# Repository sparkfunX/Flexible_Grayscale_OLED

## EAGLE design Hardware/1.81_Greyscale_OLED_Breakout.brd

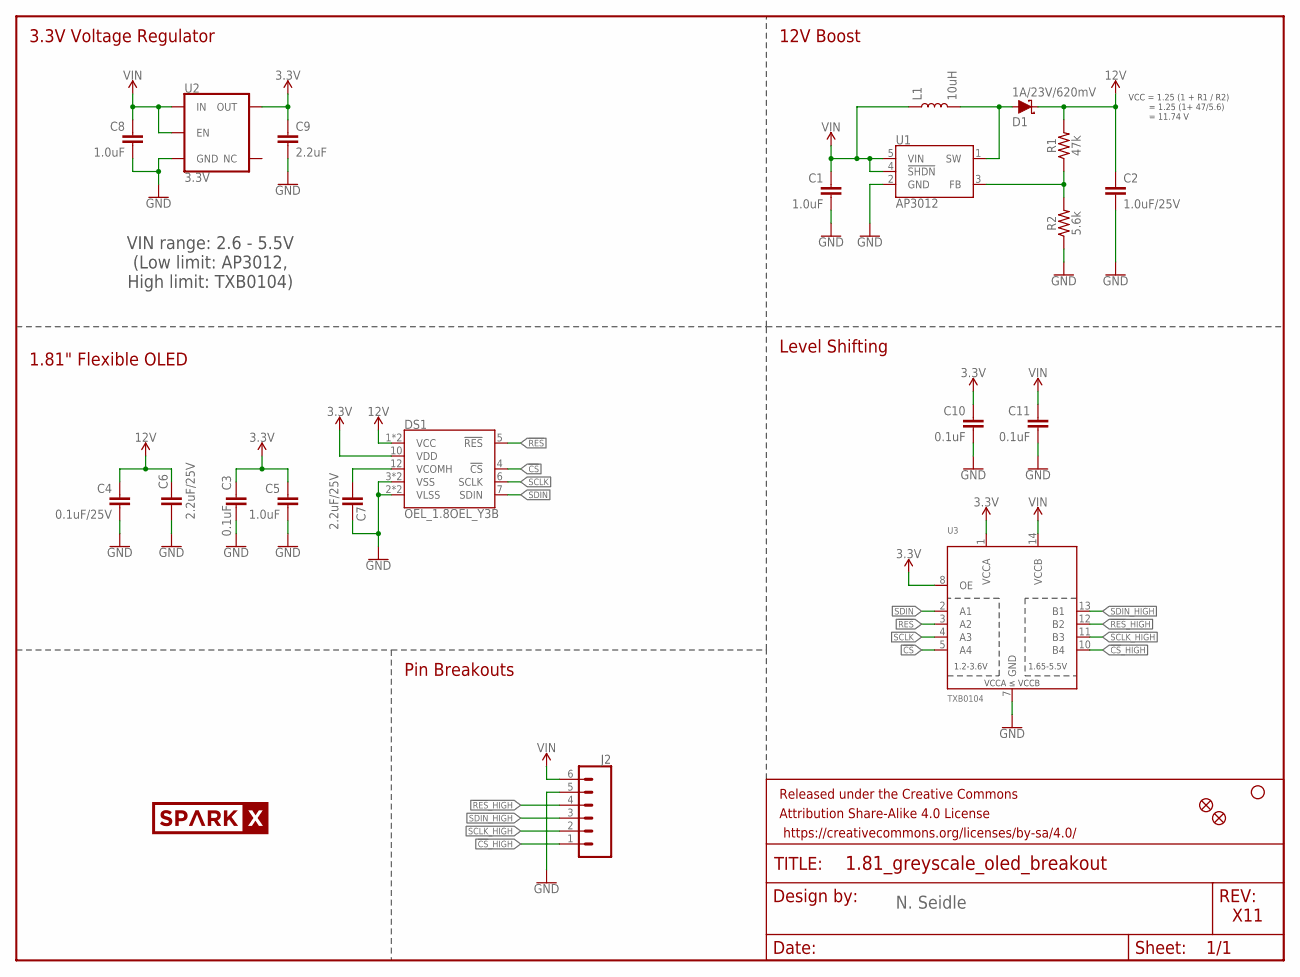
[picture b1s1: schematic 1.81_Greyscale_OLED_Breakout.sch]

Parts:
C1, C5, C8: 1.0uF; 0603
C2: 1.0uF/25V; 0805
C3, C10, C11: 0.1uF; 0603
C4: 0.1uF/25V; 0603
C6, C7: 2.2uF/25V; 0805
C9: 2.2uF; 0603
D1: 1A/23V/620mV; SOD-323
DS1: OEL_1.8OEL_Y3B; OEL_1.8_FPC_Y3B
FD1, FD2: FIDUCIAL1X2; FIDUCIAL-1X2
FRAME1: FRAME-LETTER; CREATIVE_COMMONS
H2: STAND-OFF
J2: CONN_06NO_SILK_NO_POP; 1X06_NO_SILK
L1: 10uH; INDUCTOR_3X3
LOGO1: SPARKX-LOGO5; SPARKX-LARGE
R1: 47k; 0603
R2: 5.6k; 0603
U1: AP3012; SOT23-5
U2: 3.3V; SOT23-5
U3: TXB0104; SO14

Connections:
3.3V: C3.1, C5.1, C9.1, C10.1, DS1.10 (VDD), U2.5 (OUT), U3.1 (VCCA), U3.8 (OE)
12V: C2.1, C4.1, C6.1, D1.C, DS1.1 (VCC), DS1.13 (VCC), R1.2
!CS!: DS1.4 (!CS!), U3.5 (A4)
!CS!_HIGH: J2.1, U3.10 (B4)
!RES!: DS1.5 (!RES!), U3.3 (A2)
!RES!_HIGH: J2.4, U3.12 (B2)
GND: C1.2, C2.2, C3.2, C4.2, C5.2, C6.2, C7.1, C8.2, C9.2, C10.2, C11.2, DS1.2 (VLSS), DS1.3 (VSS), DS1.8 (VSS), DS1.9 (VLSS), J2.5, R2.1, U1.2 (GND), U2.2 (GND), U3.7 (GND)
unnamed: C7.2, DS1.12 (VCOMH)
unnamed: D1.A, L1.P$2 (2), U1.1 (SW)
unnamed: R1.1, R2.2, U1.3 (FB)
SCLK: DS1.6 (SCLK), U3.4 (A3)
SCLK_HIGH: J2.2, U3.11 (B3)
SDIN: DS1.7 (SDIN), U3.2 (A1)
SDIN_HIGH: J2.3, U3.13 (B1)
VIN: C1.1, C8.1, C11.1, J2.6, L1.P$1 (1), U1.4 (!SHDN!), U1.5 (VIN), U2.1 (IN), U2.3 (EN), U3.14 (VCCB)

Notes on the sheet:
VCC = 1.25 (1 + R1 / R2) = 1.25 (1+ 47/5.6) = 11.74 V
VIN range: 2.6 - 5.5V (Low limit: AP3012, High limit: TXB0104)
3.3V Voltage Regulator
12V Boost
1.81" Flexible OLED
Level Shifting
Pin Breakouts
X11
N. Seidle

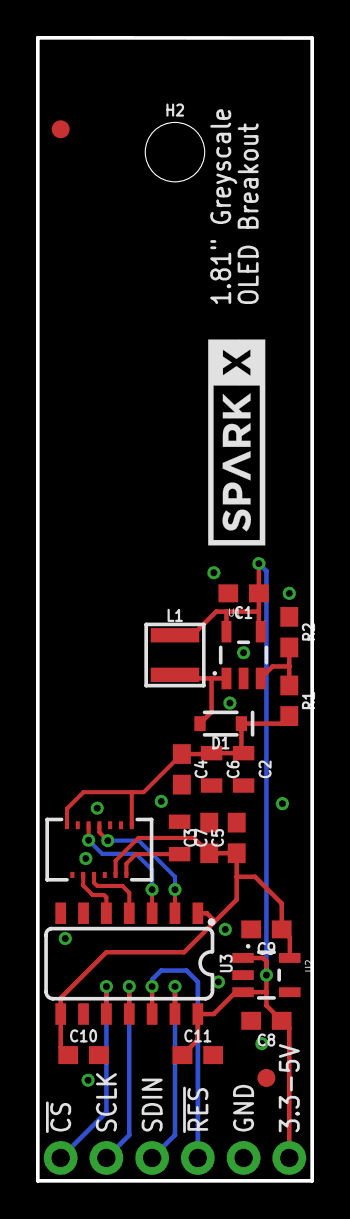
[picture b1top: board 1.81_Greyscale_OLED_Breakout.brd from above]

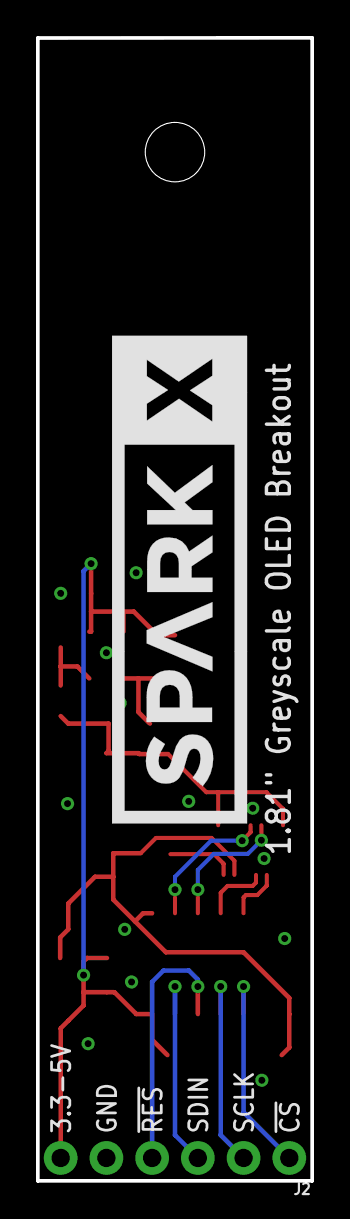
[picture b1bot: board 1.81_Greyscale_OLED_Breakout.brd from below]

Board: 2 copper layers, 15.2 x 63.5 mm, 26 parts (3 on the bottom side), 15 nets.

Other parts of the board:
LOGO2: SPARKX-LOGO5; SPARKX-XLARGE

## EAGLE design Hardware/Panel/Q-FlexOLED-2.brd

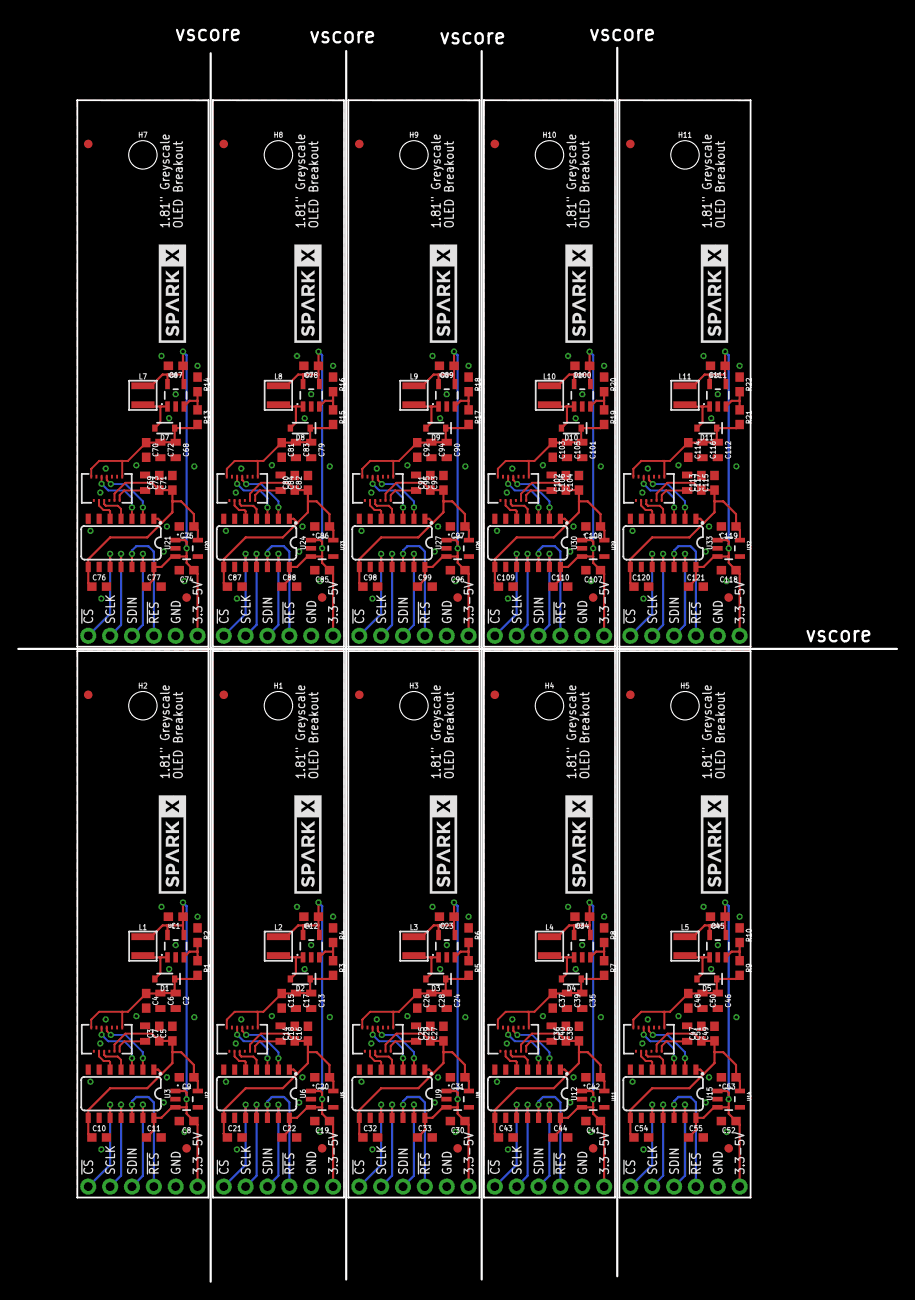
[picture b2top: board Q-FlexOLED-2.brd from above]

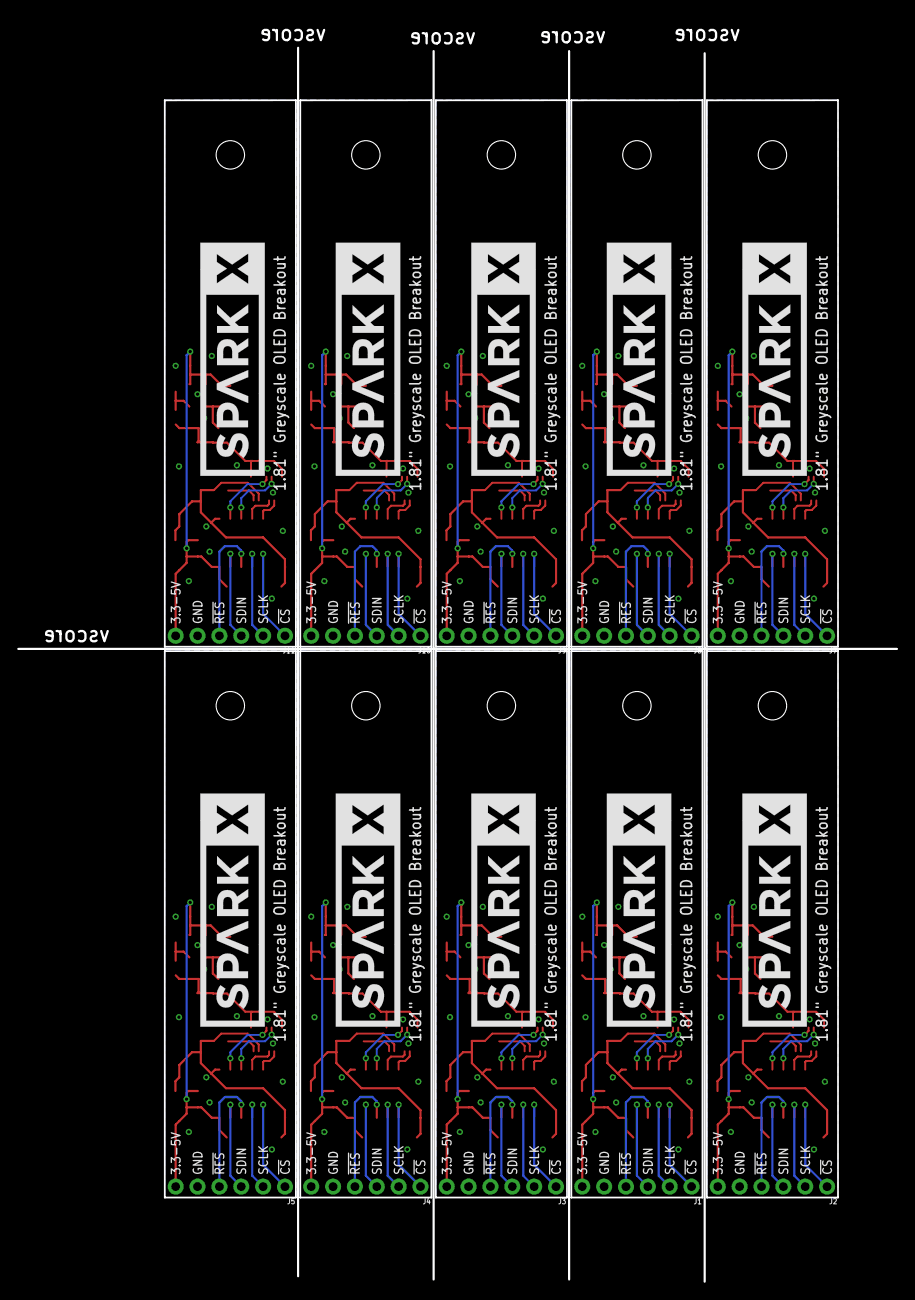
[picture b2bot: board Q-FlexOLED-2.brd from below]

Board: 2 copper layers, 102.1 x 146.8 mm, 250 parts (30 on the bottom side), 150 nets.

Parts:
C1, C5, C8, C12, C16, C19, C23, C27, C30, C34, C38, C41, C45, C49, C52, C67, C71, C74, C78, C82, C85, C89, C93, C96, C100, C104, C107, C111, C115, C118: 1.0uF; 0603
C2, C13, C24, C35, C46, C68, C79, C90, C101, C112: 1.0uF; 0805
C3, C4, C10, C11, C14, C15, C21, C22, C25, C26, C32, C33, C36, C37, C43, C44, C47, C48, C54, C55, C69, C70, C76, C77, C80, C81, C87, C88, C91, C92, C98, C99, C102, C103, C109, C110, C113, C114, C120, C121: 0.1uF; 0603
C6, C7, C17, C18, C28, C29, C39, C40, C50, C51, C72, C73, C83, C84, C94, C95, C105, C106, C116, C117: 2.2uF; 0805
C9, C20, C31, C42, C53, C75, C86, C97, C108, C119: 2.2uF; 0603
D1, D2, D3, D4, D5, D7, D8, D9, D10, D11: 1A/23V/620mV; SOD-323
DS1, DS2, DS3, DS4, DS5, DS7, DS8, DS9, DS10, DS11: OEL_1.8OEL_Y3B; OEL_1.8_FPC_Y3B
FD1, FD2, FD3, FD4, FD5, FD6, FD7, FD8, FD9, FD10, FD13, FD14, FD15, FD16, FD17, FD18, FD19, FD20, FD21, FD22: FIDUCIAL1X2; FIDUCIAL-1X2
H1, H2, H3, H4, H5, H7, H8, H9, H10, H11: STAND-OFF
J1, J2, J3, J4, J5, J7, J8, J9, J10, J11: 1X06_NO_SILK
L1, L2, L3, L4, L5, L7, L8, L9, L10, L11: 10uH; INDUCTOR_3X3
LOGO1, LOGO3, LOGO5, LOGO7, LOGO9, LOGO13, LOGO15, LOGO17, LOGO19, LOGO21: SPARKX-LOGO5; SPARKX-LARGE
LOGO2, LOGO4, LOGO6, LOGO8, LOGO10, LOGO14, LOGO16, LOGO18, LOGO20, LOGO22: SPARKX-LOGO5; SPARKX-XLARGE
R1, R3, R5, R7, R9, R13, R15, R17, R19, R21: 47k; 0603
R2, R4, R6, R8, R10, R14, R16, R18, R20, R22: 5.6k; 0603
U1, U4, U7, U10, U13, U19, U22, U25, U28, U31: AP3012; SOT23-5
U2, U5, U8, U11, U14, U20, U23, U26, U29, U32: 3.3V; SOT23-5
U3, U6, U9, U12, U15, U21, U24, U27, U30, U33: TXB0104; SO14

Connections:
3.3V: C3.1, C5.1, C9.1, C10.1, DS1.10, U2.5, U3.1, U3.8
3.3V1: C14.1, C16.1, C20.1, C21.1, DS2.10, U5.5, U6.1, U6.8
3.3V2: C25.1, C27.1, C31.1, C32.1, DS3.10, U8.5, U9.1, U9.8
3.3V3: C36.1, C38.1, C42.1, C43.1, DS4.10, U11.5, U12.1, U12.8
3.3V4: C47.1, C49.1, C53.1, C54.1, DS5.10, U14.5, U15.1, U15.8
3.3V6: C69.1, C71.1, C75.1, C76.1, DS7.10, U20.5, U21.1, U21.8
3.3V7: C80.1, C82.1, C86.1, C87.1, DS8.10, U23.5, U24.1, U24.8
3.3V8: C91.1, C93.1, C97.1, C98.1, DS9.10, U26.5, U27.1, U27.8
3.3V9: C102.1, C104.1, C108.1, C109.1, DS10.10, U29.5, U30.1, U30.8
3.3V10: C113.1, C115.1, C119.1, C120.1, DS11.10, U32.5, U33.1, U33.8
12V: C2.1, C4.1, C6.1, D1.C, DS1.1, DS1.13, R1.2
12V1: C13.1, C15.1, C17.1, D2.C, DS2.1, DS2.13, R3.2
12V2: C24.1, C26.1, C28.1, D3.C, DS3.1, DS3.13, R5.2
12V3: C35.1, C37.1, C39.1, D4.C, DS4.1, DS4.13, R7.2
12V4: C46.1, C48.1, C50.1, D5.C, DS5.1, DS5.13, R9.2
12V6: C68.1, C70.1, C72.1, D7.C, DS7.1, DS7.13, R13.2
12V7: C79.1, C81.1, C83.1, D8.C, DS8.1, DS8.13, R15.2
12V8: C90.1, C92.1, C94.1, D9.C, DS9.1, DS9.13, R17.2
12V9: C101.1, C103.1, C105.1, D10.C, DS10.1, DS10.13, R19.2
12V10: C112.1, C114.1, C116.1, D11.C, DS11.1, DS11.13, R21.2
!CS!: DS1.4, U3.5
!CS!1: DS2.4, U6.5
!CS!2: DS3.4, U9.5
!CS!3: DS4.4, U12.5
!CS!4: DS5.4, U15.5
!CS!6: DS7.4, U21.5
!CS!7: DS8.4, U24.5
!CS!8: DS9.4, U27.5
!CS!9: DS10.4, U30.5
!CS!10: DS11.4, U33.5
!CS!_HIGH: J2.1, U3.10
!CS!_HIGH1: J1.1, U6.10
!CS!_HIGH2: J3.1, U9.10
!CS!_HIGH3: J4.1, U12.10
!CS!_HIGH4: J5.1, U15.10
!CS!_HIGH6: J7.1, U21.10
!CS!_HIGH7: J8.1, U24.10
!CS!_HIGH8: J9.1, U27.10
!CS!_HIGH9: J10.1, U30.10
!CS!_HIGH10: J11.1, U33.10
!RES!: DS1.5, U3.3
!RES!1: DS2.5, U6.3
!RES!2: DS3.5, U9.3
!RES!3: DS4.5, U12.3
!RES!4: DS5.5, U15.3
!RES!6: DS7.5, U21.3
!RES!7: DS8.5, U24.3
!RES!8: DS9.5, U27.3
!RES!9: DS10.5, U30.3
!RES!10: DS11.5, U33.3
!RES!_HIGH: J2.4, U3.12
!RES!_HIGH1: J1.4, U6.12
!RES!_HIGH2: J3.4, U9.12
!RES!_HIGH3: J4.4, U12.12
!RES!_HIGH4: J5.4, U15.12
!RES!_HIGH6: J7.4, U21.12
!RES!_HIGH7: J8.4, U24.12
!RES!_HIGH8: J9.4, U27.12
!RES!_HIGH9: J10.4, U30.12
!RES!_HIGH10: J11.4, U33.12
GND: C1.2, C2.2, C3.2, C4.2, C5.2, C6.2, C7.1, C8.2, C9.2, C10.2, C11.2, DS1.2, DS1.3, DS1.8, DS1.9, J2.5, R2.1, U1.2, U2.2, U3.7
GND1: C12.2, C13.2, C14.2, C15.2, C16.2, C17.2, C18.1, C19.2, C20.2, C21.2, C22.2, DS2.2, DS2.3, DS2.8, DS2.9, J1.5, R4.1, U4.2, U5.2, U6.7
GND2: C23.2, C24.2, C25.2, C26.2, C27.2, C28.2, C29.1, C30.2, C31.2, C32.2, C33.2, DS3.2, DS3.3, DS3.8, DS3.9, J3.5, R6.1, U7.2, U8.2, U9.7
GND3: C34.2, C35.2, C36.2, C37.2, C38.2, C39.2, C40.1, C41.2, C42.2, C43.2, C44.2, DS4.2, DS4.3, DS4.8, DS4.9, J4.5, R8.1, U10.2, U11.2, U12.7
GND4: C45.2, C46.2, C47.2, C48.2, C49.2, C50.2, C51.1, C52.2, C53.2, C54.2, C55.2, DS5.2, DS5.3, DS5.8, DS5.9, J5.5, R10.1, U13.2, U14.2, U15.7
GND6: C67.2, C68.2, C69.2, C70.2, C71.2, C72.2, C73.1, C74.2, C75.2, C76.2, C77.2, DS7.2, DS7.3, DS7.8, DS7.9, J7.5, R14.1, U19.2, U20.2, U21.7
GND7: C78.2, C79.2, C80.2, C81.2, C82.2, C83.2, C84.1, C85.2, C86.2, C87.2, C88.2, DS8.2, DS8.3, DS8.8, DS8.9, J8.5, R16.1, U22.2, U23.2, U24.7
GND8: C89.2, C90.2, C91.2, C92.2, C93.2, C94.2, C95.1, C96.2, C97.2, C98.2, C99.2, DS9.2, DS9.3, DS9.8, DS9.9, J9.5, R18.1, U25.2, U26.2, U27.7
GND9: C100.2, C101.2, C102.2, C103.2, C104.2, C105.2, C106.1, C107.2, C108.2, C109.2, C110.2, DS10.2, DS10.3, DS10.8, DS10.9, J10.5, R20.1, U28.2, U29.2, U30.7
GND10: C111.2, C112.2, C113.2, C114.2, C115.2, C116.2, C117.1, C118.2, C119.2, C120.2, C121.2, DS11.2, DS11.3, DS11.8, DS11.9, J11.5, R22.1, U31.2, U32.2, U33.7
unnamed: C7.2, DS1.12
unnamed: D1.A, L1.P$2, U1.1
unnamed: R1.1, R2.2, U1.3
unnamed: D2.A, L2.P$2, U4.1
unnamed: R3.1, R4.2, U4.3
unnamed: C18.2, DS2.12
unnamed: D3.A, L3.P$2, U7.1
unnamed: R5.1, R6.2, U7.3
unnamed: C29.2, DS3.12
unnamed: D4.A, L4.P$2, U10.1
unnamed: R7.1, R8.2, U10.3
unnamed: C40.2, DS4.12
unnamed: D5.A, L5.P$2, U13.1
unnamed: R9.1, R10.2, U13.3
unnamed: C51.2, DS5.12
unnamed: D7.A, L7.P$2, U19.1
unnamed: R13.1, R14.2, U19.3
unnamed: C73.2, DS7.12
unnamed: D8.A, L8.P$2, U22.1
unnamed: R15.1, R16.2, U22.3
unnamed: C84.2, DS8.12
unnamed: D9.A, L9.P$2, U25.1
unnamed: R17.1, R18.2, U25.3
unnamed: C95.2, DS9.12
unnamed: D10.A, L10.P$2, U28.1
unnamed: R19.1, R20.2, U28.3
unnamed: C106.2, DS10.12
unnamed: D11.A, L11.P$2, U31.1
unnamed: R21.1, R22.2, U31.3
unnamed: C117.2, DS11.12
SCLK: DS1.6, U3.4
SCLK1: DS2.6, U6.4
SCLK2: DS3.6, U9.4
SCLK3: DS4.6, U12.4
SCLK4: DS5.6, U15.4
SCLK6: DS7.6, U21.4
SCLK7: DS8.6, U24.4
SCLK8: DS9.6, U27.4
SCLK9: DS10.6, U30.4
SCLK10: DS11.6, U33.4
SCLK_HIGH: J2.2, U3.11
SCLK_HIGH1: J1.2, U6.11
SCLK_HIGH2: J3.2, U9.11
SCLK_HIGH3: J4.2, U12.11
SCLK_HIGH4: J5.2, U15.11
SCLK_HIGH6: J7.2, U21.11
SCLK_HIGH7: J8.2, U24.11
SCLK_HIGH8: J9.2, U27.11
SCLK_HIGH9: J10.2, U30.11
SCLK_HIGH10: J11.2, U33.11
SDIN: DS1.7, U3.2
SDIN1: DS2.7, U6.2
SDIN2: DS3.7, U9.2
SDIN3: DS4.7, U12.2
SDIN4: DS5.7, U15.2
SDIN6: DS7.7, U21.2
SDIN7: DS8.7, U24.2
SDIN8: DS9.7, U27.2
SDIN9: DS10.7, U30.2
SDIN10: DS11.7, U33.2
SDIN_HIGH: J2.3, U3.13
SDIN_HIGH1: J1.3, U6.13
SDIN_HIGH2: J3.3, U9.13
SDIN_HIGH3: J4.3, U12.13
SDIN_HIGH4: J5.3, U15.13
SDIN_HIGH6: J7.3, U21.13
SDIN_HIGH7: J8.3, U24.13
SDIN_HIGH8: J9.3, U27.13
SDIN_HIGH9: J10.3, U30.13
SDIN_HIGH10: J11.3, U33.13
VIN: C1.1, C8.1, C11.1, J2.6, L1.P$1, U1.4, U1.5, U2.1, U2.3, U3.14
VIN1: C12.1, C19.1, C22.1, J1.6, L2.P$1, U4.4, U4.5, U5.1, U5.3, U6.14
VIN2: C23.1, C30.1, C33.1, J3.6, L3.P$1, U7.4, U7.5, U8.1, U8.3, U9.14
VIN3: C34.1, C41.1, C44.1, J4.6, L4.P$1, U10.4, U10.5, U11.1, U11.3, U12.14
VIN4: C45.1, C52.1, C55.1, J5.6, L5.P$1, U13.4, U13.5, U14.1, U14.3, U15.14
VIN6: C67.1, C74.1, C77.1, J7.6, L7.P$1, U19.4, U19.5, U20.1, U20.3, U21.14
VIN7: C78.1, C85.1, C88.1, J8.6, L8.P$1, U22.4, U22.5, U23.1, U23.3, U24.14
VIN8: C89.1, C96.1, C99.1, J9.6, L9.P$1, U25.4, U25.5, U26.1, U26.3, U27.14
VIN9: C100.1, C107.1, C110.1, J10.6, L10.P$1, U28.4, U28.5, U29.1, U29.3, U30.14
VIN10: C111.1, C118.1, C121.1, J11.6, L11.P$1, U31.4, U31.5, U32.1, U32.3, U33.14

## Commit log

2017-11-22 :boom::camel: Added .gitattributes & .gitignore files
2017-11-22 Updating readme
2018-01-15 Made board smaller. Increased FPC footprint size.

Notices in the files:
parts and their libraries:
SparkFun-Aesthetics: Licensing: Creative Commons ShareAlike 4.0 International - https://creativecommons.org/licenses/by-sa/4.0
SparkFun-Aesthetics: Released under the Creative Commons Attribution Share-Alike 4.0 License
SparkFun-Aesthetics: https://creativecommons.org/licenses/by-sa/4.0
